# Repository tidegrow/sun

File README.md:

# Tidegrow Sun

Tidegrow Sun is an experimental low-power grow light.

## Pinout

Sun uses a non-standard MicroUSB pinout that is compatible with [Tidegrow Curator](https://github.com/tidegrow/curator):

| Signal | Description |
| ------ | ----------- |
| VBUS | Power (5V) |
| D+ | LED PWM control input (3.3V) |
| D- | Photoresistor output (0-3.3V) |
| GND | Ground |

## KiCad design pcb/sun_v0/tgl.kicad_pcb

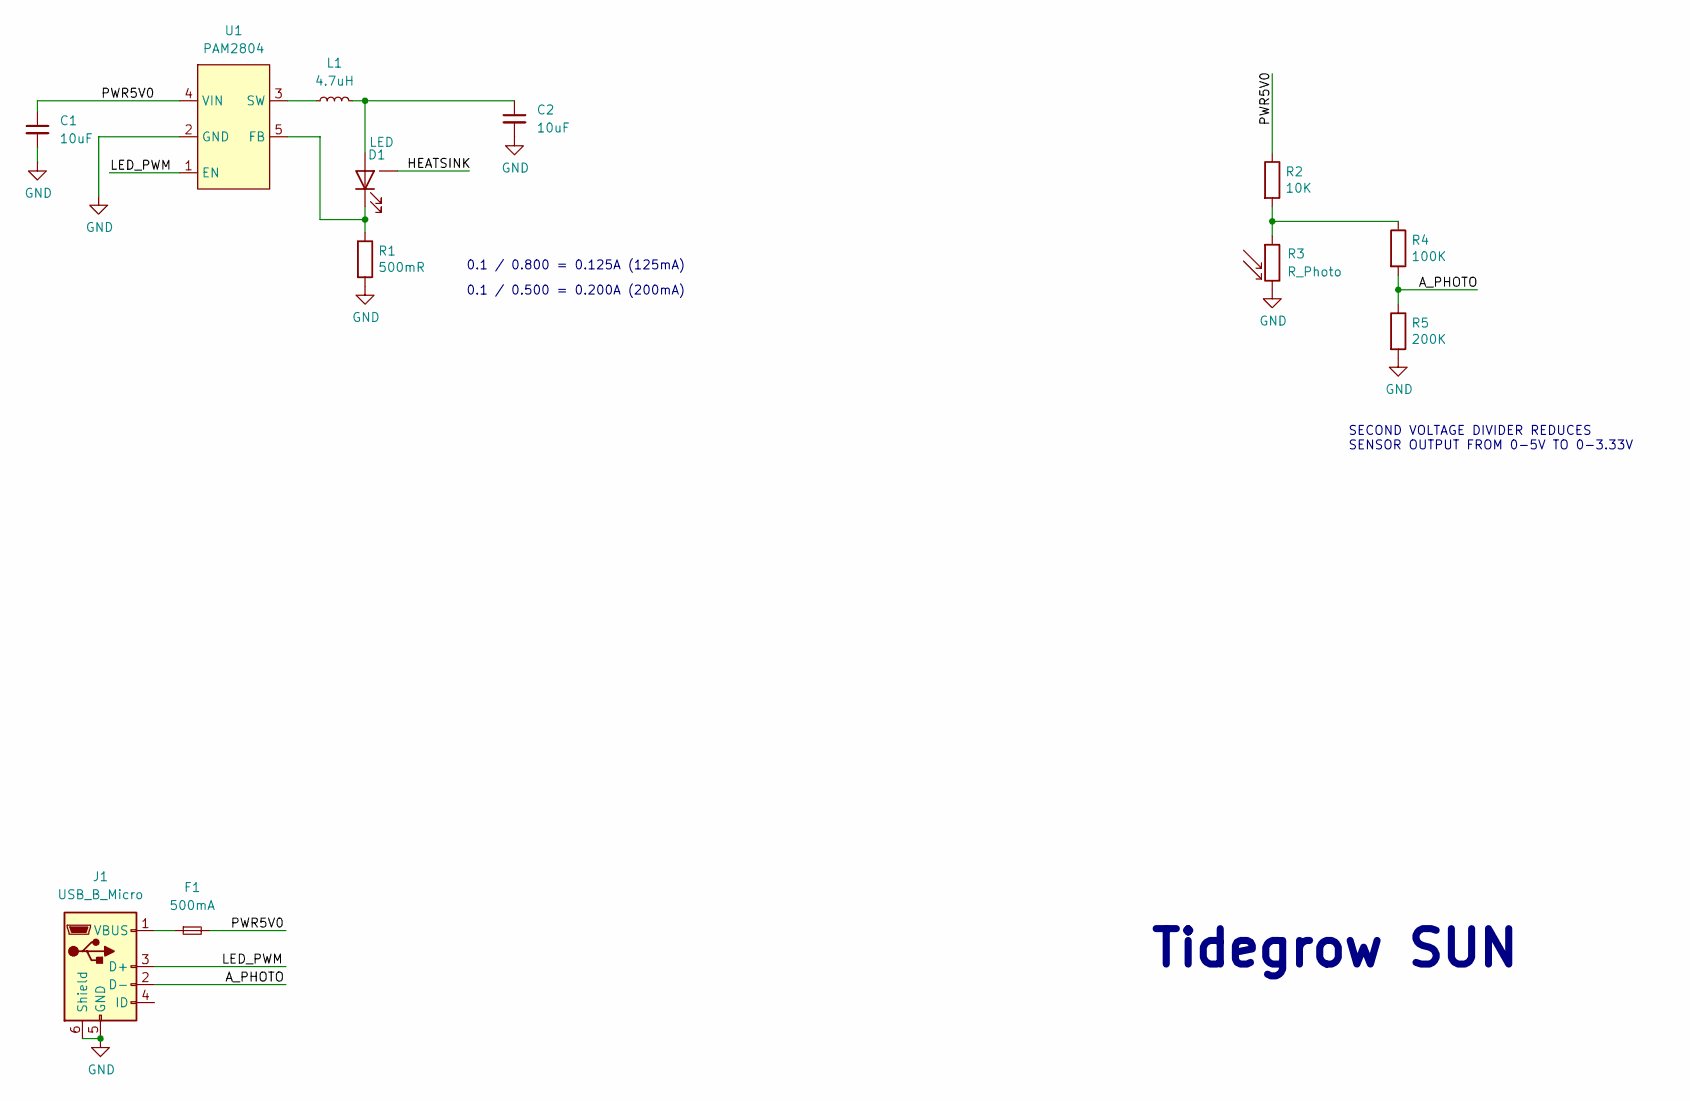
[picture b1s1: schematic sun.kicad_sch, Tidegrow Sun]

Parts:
C1, C2: 10uF; C_0603_1608Metric
D1: LED; LED_1W_3W_R8
F1: 500mA; Fuse_0805_2012Metric
J1: USB_B_Micro; Generic_Chinese_USB_MicroB_Horizontal_Socket_Circular_Holes
L1: 4.7uH; L_1008_2520Metric
R1: 500mR; R_2010_5025Metric
R2: 10K; R_0603_1608Metric
R3: R_Photo; R_PHOTO_3624
R4: 100K; R_0603_1608Metric
R5: 200K; R_0603_1608Metric
U1: PAM2804; SOT-23-5

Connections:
/A_PHOTO: J1.2 (D-), R4.2, R5.1
/HEATSINK: D1.3 (HEATSINK)
/LED_PWM: J1.3 (D+), U1.1 (EN)
/PWR5V0: C1.1, F1.2, R2.1, U1.4 (VIN)
GND: C1.2, C2.2, J1.5 (GND), J1.6 (Shield), R1.2, R3.2, R5.2, U1.2 (GND)
unnamed: C2.1, D1.2 (A), L1.2
unnamed: D1.1 (K), R1.1, U1.5 (FB)
unnamed: F1.1, J1.1 (VBUS)
unnamed: L1.1, U1.3 (SW)
unnamed: R2.2, R3.1, R4.1

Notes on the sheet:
SECOND VOLTAGE DIVIDER REDUCES SENSOR OUTPUT FROM 0-5V TO 0-3.33V
0.1 / 0.800 = 0.125A (125mA)
Tidegrow SUN
0.1 / 0.500 = 0.200A (200mA)

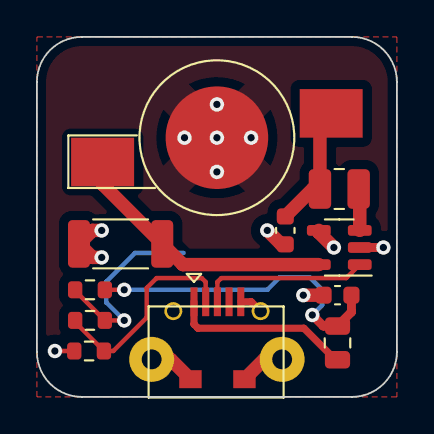
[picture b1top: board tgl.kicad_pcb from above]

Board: 2 copper layers, 20.0 x 20.0 mm, 12 parts (1 on the bottom side), 9 nets.

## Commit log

2023-05-20 add pcb
2023-05-20 rename pcb

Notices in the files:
pcb/sun_v0/sun.kicad_sch:
Copyright © 2022 Lone Dynamics Corporation
